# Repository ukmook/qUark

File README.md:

# qUark Flight Electronics

 ## THIS COMES WITH NO WARRANTY! BUILD, FLY, AND USE AT YOUR OWN RISK!

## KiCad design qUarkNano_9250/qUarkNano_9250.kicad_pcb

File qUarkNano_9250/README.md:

## qUarkNano flight controller

 #### Design files for qUarkNano 9250 Flight controller.

This is not an easy build and uses very small components.

I use a small oven which i bought from a local store, a microscope from ebay and solder paste from an online UK store.
But if you are thinking of building this then i suspect that you already have the right tools.

The BOM file has all the part numbers listed either from RS Components or mouser (the 2 component suppliers i use), You do not have to buy from there but adding the part numbers to the RS website search will bring up the item page which has all the info. The components can be bought from where ever you like.

 ### Kicad

 I have included the design files for Kicad and also images, 3d for freecad, part footprint .pretty, PDF schematic and Plots for stencils etc.

 ### Specs

4 PWM, 3 Uarts, 1 RCIN This design has been tested extensively with S800, S84 and mini quads

The design has been optimised for Ardupilot, The uarts, i2c and spi buses were chosen to keep the DMA Table as clear as possible.

 Link to HWDEF in my fork of Ardupilot <https://github.com/ukmook/ardupilot/tree/master/libraries/AP_HAL_ChibiOS/hwdef/qUarkf4_Nano9>

Other flight stacks can be used.

  # Features

  | Specification |  |
| ------ | ------ |
| IMU | MPU9250 |
| Baro | BMP280 |
| SD Card | Push Push type JST |
| Volt Sense | Voltage sensor 6s Max |
| Curent Sense | 3.3v |
| Uarts | Usart1 Usart2 Usart6 |
| RX | RCIN on 3 pin port |
| CPU | STM32F405RGT6 |
| PWM | 4 PWM |
| I2C | 1 I2C bus |
| USB | Vertical USB with diode protection |
| PCB Size | 4 layer board of 21.6 x 30.1 mm. |
| Buzzer/Alarm | Alarm for Ardupilot musical tones on a timer using micro nfet |

 # PCB

PCB Boards OSH Park https://oshpark.com/shared_projects/hUyCWNei

 # Upper

 # Lower

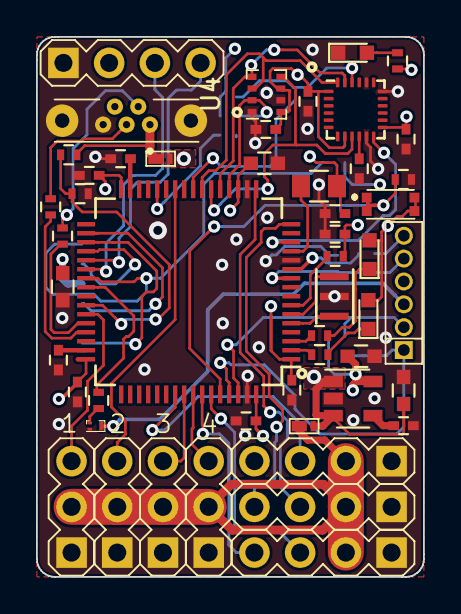
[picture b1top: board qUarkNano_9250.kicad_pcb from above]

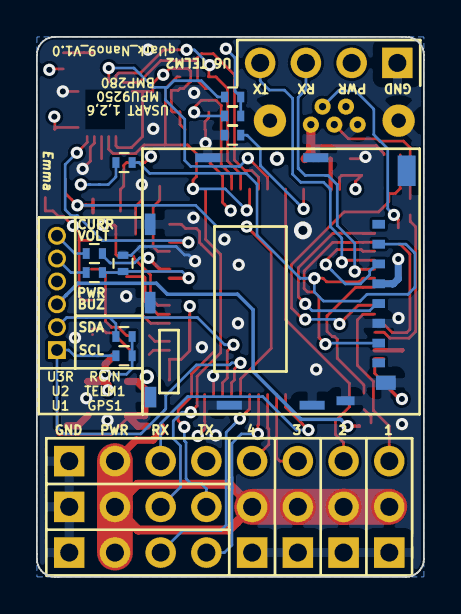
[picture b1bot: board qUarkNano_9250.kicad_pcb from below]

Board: 4 copper layers, 21.5 x 30.0 mm, 60 parts (10 on the bottom side), 55 nets.

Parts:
C1, C2: 0402_2.2uF_X5R; CAP_0402
C3, C4, C6, C10: 0402_100nF_X5R; CAP_0402
C5: 0402_10nF_X5R; CAP_0402
C7, C9: 0603_100nF_X7R; CAP_0603_100nF
C8: 0402_10nF_X5R; CAP_0402_10nF
C11, C12: 0603_4.7uF_X5R; CAP_0603
C13, C14, C15, C16, C17: 0402_100nF_X7R; CAP_0402
D1: Red_LED_0603; RED_LED_0603
D2: Blue_LED_0603; BLUE_LED_0603
D3: Green_LED_0603; GREEN_LED_0603
D4, D5: SDM1U20CSP-7
FB1: Ferrite_Bead_0805_Wurth; FERRITE_0805
J1: SD_CARD_JST; JST_SDCARD
J2, J3, J4, J5: PIN_2.54x3_VRT; Pin_Header_Straight_1x03_Pitch2.54mm
J6, J7, J8, J9: PIN_2.54x4_VRT; Pin_Header_Straight_1x04_Pitch2.54mm
J10: USB_A_VRT_WURTH; WURTH_USB_VRT
J12: CONN_1.27_6; Pin_Header_Straight_1x06_Pitch1.27mm
Q1: NFET_CSD13383F4_MICRO; NFET_CSD13383F4
R1, R5, R8, R9, R10, R11: 0402_10K
R2, R3, R4: 0402_330R
R6, R7: 0402_22R
R12, R13: 0402_4k7; 0402_4K7
R14: 0402_1K1
R15: 0402_1K
R16: 0402_9K1
R17, R18, R19: 0402_2K
S1: EVPBB2A9B000
U1: MPU9250
U2: STM32F405RGT6
U3: REG113NA-3.3_250; REG113NA_3_3_250
U4: BMP280
Y1: CSTCE16M0V53A-R0

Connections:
+5V_MIX: C7.1, D4.1, D5.1, U3.1, U3.3
BLUE: R3.2, U2.3
BMP280_CS: R9.1, U2.20, U4.2
BOOT1: R5.1, S1.1, S1.3, U2.60
BOOT1_PD: R8.1, U2.28
BUZZER: R17.2, U2.40
COIL: J12.3, Q1.3
CURR: J12.6, R15.2
GND: C1.2, C2.2, C3.2, C4.1, C5.2, C6.2, C7.2, C8.2, C9.2, C10.2, C11.2, C12.2, C13.2, C14.2, C15.2, C16.2, C17.1, D3.1, J1.6, J1.9, J1.10, J1.11, J1.12, J1.13, J1.14, J1.15, J1.16, J1.17, J1.18, J2.1, J3.1, J4.1, J5.1, J6.1, J7.1, J8.1, J9.1, J10.5, J10.6, J10.7, Q1.2, R5.2, R8.2, R14.2, R18.1, U1.11, U1.18, U1.20, U2.12, U2.18, U2.63, U3.2, U4.1, U4.7, Y1.2
I2C1_SCL: J12.1, R13.2, U2.61
I2C1_SDA: J12.2, R12.2, U2.62
INT_MPU9250: U1.12, U2.14
MISO1: U1.9, U2.22, U4.5
MISO2: J1.7, U2.35
MOSI1: U1.24, U2.23, U4.3
MOSI2: J1.3, U2.36
MPU9250_CS: R11.1, U1.22, U2.24
NRST: R1.2, U2.7
unnamed: C1.1, U2.31
unnamed: C2.1, U2.47
unnamed: C4.2, U1.10
unnamed: C8.1, U3.4
unnamed: D1.1, R2.1
unnamed: D2.1, R3.1
unnamed: D3.2, R4.2
unnamed: FB1.2, U2.13
unnamed: Q1.1, R17.1
unnamed: R15.1, U2.11
unnamed: U2.5, Y1.1
unnamed: U2.6, Y1.3
PWM1: J2.3, U2.43
PWM2: J3.3, U2.26
PWM3: J4.3, U2.56
PWM4: J5.3, U2.57
RCIN: J8.3, U2.55
RED: R2.2, U2.2
RX1: J6.3, U2.59
RX2: J7.3, U2.17
RX6: J9.3, U2.38
SCK1: U1.23, U2.21, U4.4
SCK2: J1.5, U2.34
SDCARD_CS: J1.2, R10.2, U2.39
SERVO_PWR: D5.2, J2.2, J3.2, J4.2, J5.2, J6.2, J7.2, J8.2, J9.2, J12.4
TX1: J6.4, U2.58
TX2: J7.4, U2.16
TX6: J9.4, U2.37
USBDM: J10.2, R7.2
USBDM1: R7.1, U2.44
USBDP: J10.3, R6.2
USBDP1: R6.1, U2.45
VBUS: D4.2, J10.1, R19.1
VBUS_O: R18.2, R19.2, U2.42
VCC: C3.1, C5.1, C6.1, C9.1, C10.1, C11.1, C12.1, C13.1, C14.1, C15.1, C16.1, C17.2, D1.2, D2.2, FB1.1, J1.4, R1.1, R4.1, R9.2, R10.1, R11.2, R12.1, R13.1, S1.2, S1.4, U1.1, U1.8, U1.13, U2.1, U2.19, U2.32, U2.48, U2.64, U3.5, U4.6, U4.8
VOLT: J12.5, R16.2
VOLTO: R14.1, R16.1, U2.10

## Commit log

2019-05-08 SCH_PDF : add quark nano UC4H
2019-05-08 SCH_Kicad : Add qUark Nano UC4H schematic
2019-05-08 PCD_Kicad : add qUark Nano UC4H kicad_pcb
2019-05-12 Readme changes
2019-05-12 Remove old files and update with new design V1.1
2019-05-15 Edit readme files
2019-05-15 Add images to readme
2019-05-15 Update readme and images
2019-05-15 Update front page readme
2019-05-15 Add qUarkNano_9250 flight controller
2019-05-15 Remove unused files
2019-05-15 Update 9250 readme
2019-05-15 Update UC4H Readme to quark format
2019-05-15 Add link to HWDEF in fork of Ardupilot
2019-05-26 Add initial commit for qUarkMini_BMI088
2019-05-26 Add links to HWDEF
2019-05-26 Add complimentary files for qUarkMini_BMI
2019-05-26 Add warranty info
2019-05-26 Reduce size of warranty
2019-06-22 Update flight controller naming qUarkMini_Wing_V2
2019-06-22 Fix Typo
2019-06-22 Add images to qUarkMini_Wing_V2 flight controller
2020-01-02 Update Readme and add firmware for Nano UC4H
2020-01-02 Add image to Nano UC4H readme
2020-01-02 Change wing V2 readme
2020-01-02 Add image to quark mini wing readme
2020-01-04 AP_Periph Bluepill CANBUS setup first draft
2020-01-04 Have to clear image copyright
2020-01-05 Cleared copyright from Olliw
2020-01-05 WIP 2 Blue-pill readme
2020-01-05 WIP 3 Blue-Pill readme
2020-01-05 WIP Change for correct image
2020-01-05 WIP 4 Blue-Pill Readme
2020-01-05 Add stm-flasher instructions
2020-01-05 Typo
2020-01-05 Grammer
2020-01-05 Add complete instructions for STM-Flasher
2020-01-05 First read through
2020-01-05 Important note on not powering down
2020-01-05 Second read through
2020-03-28 Add 4.0.5 Plane Firmware & bootloaders for qUarkMini_Wing boards
2020-03-28 Add zip folders
2020-05-13 AP_Periph: Rangefinder test f303
2020-05-22 First View mav to msp
2020-05-22 Second View
2020-05-22 Add image
2020-05-23 Final read through
2020-05-23 Fixed typos
2020-05-24 Fixed errors
2020-05-24 Final
2020-05-24 Make it easier for user to follow libraries
2020-05-24 Add quark QMWV4 4.0.5 plane firmware
2020-05-30 Update Readme
    Add custom osd instruction.
2020-07-31 Add zip files of qUark FW
2020-12-04 Add pixracer-periph fw
2022-10-09 Add bin files
2023-02-07 Start changes
